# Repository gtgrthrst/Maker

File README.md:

# Maker

歡迎來到我的分享空間

在這邊分享一些我自己做的專案

目前先放置溫溼度二氧化碳、溫濕度偵測器

在4*4*10cm空間中整合了LOLIN32模組跟溫溼度二氧化碳偵測器

並預留了5V、3.3風扇接腳

目前可以SSD1306 OLED 0.96" ST7735 TFT LCD 1.8" 彩屏做顯示

還有預留SHTC3跟SHT4X的腳位可以使用

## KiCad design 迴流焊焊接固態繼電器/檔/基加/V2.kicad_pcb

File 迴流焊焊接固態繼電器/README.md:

# 自製迴流焊台

使用NTC串並聯電路作為感溫器

SSD1306做為顯示

配有一按鍵鍵與旋轉編碼器做為未來溫度控制的開關與調整用

板上搭配220V 5A的固態繼電器與保險絲做為加熱板的控制

110Vto5V 3W的開關電源做整個系統的供電

目前使用樹莓派Pi Pico或相容RP2040作為主控

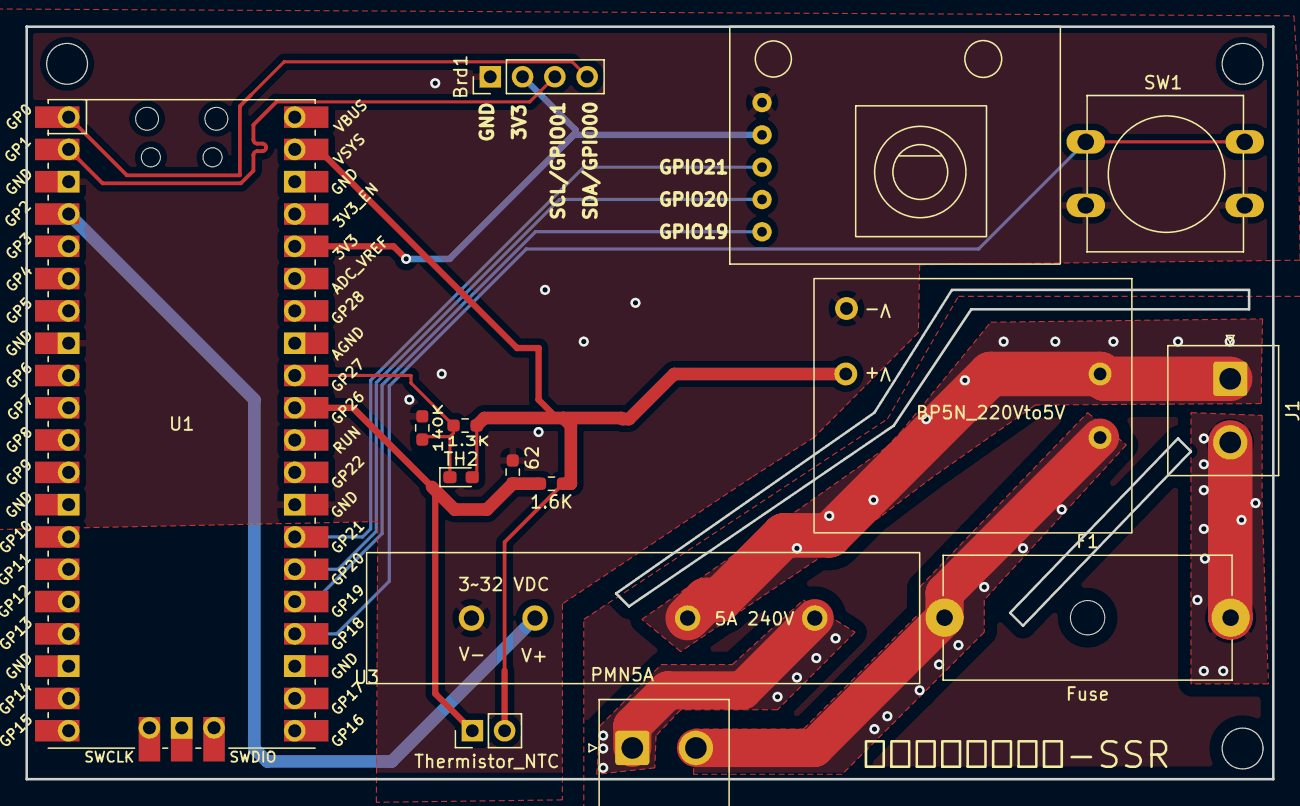
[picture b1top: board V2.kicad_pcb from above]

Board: 2 copper layers, 98.0 x 59.2 mm, 15 parts (0 on the bottom side), 16 nets.

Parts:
Brd1: SSD1306; PinHeader_1x04_P2.54mm_Vertical
F1: Fuse; Fuseholder_Cylinder-5x20mm_Schurter_0031_8201_Horizontal_Op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
J1, J2: Conn_01x02_Female; JST_NV_B02P-NV_1x02_P5.00mm_Vertical
R4: 1.6K; R_0603_1608Metric_Pad0.98x0.95mm_HandSolder
R5: 62; R_0603_1608Metric_Pad0.98x0.95mm_HandSolder
R6: 1.3K; R_0603_1608Metric_Pad0.98x0.95mm_HandSolder
R7: 140K; R_0603_1608Metric_Pad0.98x0.95mm_HandSolder
SW1: SW_Push_Dual_x2; SW_PUSH-12mm
TH1: Thermistor_NTC; PinHeader_1x02_P2.54mm_Vertical
TH2: Thermistor_NTC; LED_0603_1608Metric_Pad1.05x0.95mm_HandSolder
U1: Pico; RPi_Pico_SMD_TH
U2: BP5N_220Vto5V; PB5N_220Vto5V
U3: PMN5A2032_relay_SSR; PMN5A_relay_SSR
U5: Rotary_encoder; Encoder_360

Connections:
3V3: Brd1.2 (VCC), U1.36 (3V3), U5.4 (+)
5V: R4.2, R6.2, TH1.2, TH2.2, U1.39 (VSYS), U2.3 (5V+)
110+: J1.1, U2.1 (N), U3.3 (110+)
110-: F1.1, J2.2, U2.2 (L)
/110-_2: J2.1, U3.4 (110-)
/110-_3: F1.2, J1.2
ADC0: R4.1, R5.1, TH1.1, U1.31 (GPIO26_ADC0)
ADC1: R6.1, R7.1, TH2.1, U1.32 (GPIO27_ADC1)
GND: Brd1.1 (GND), R5.2, R7.2, SW1.2 (D), U1.3 (GND), U1.8 (GND), U1.28 (GND), U2.4 (5V-), U3.1 (3V-), U5.5 (GND)
GPIO2: U1.4 (GPIO2), U3.2 (3V+)
GPIO18: SW1.1 (C), U1.24 (GPIO18)
GPIO19: U1.25 (GPIO19), U5.1 (CLK)
GPIO20: U1.26 (GPIO20), U5.2 (DT)
GPIO21: U1.27 (GPIO21), U5.3 (SW)
SCL: Brd1.3 (SCL), U1.2 (GPIO1)
SDA: Brd1.4 (SDA), U1.1 (GPIO0)

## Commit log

2022-12-20 Create ReflowSoldering_SSR
2024-09-15 Create FreeCAD
